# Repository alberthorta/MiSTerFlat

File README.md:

# MiSTerFlat

Everything for my flat MiSTer FPGA: the boards, the display, the web manager and the helper
scripts, in one repository.

| Folder | What it is |
|---|---|
| [`hardware/`](hardware) | The flat backplane (Rev A5) and the front panel board. KiCad projects generated by Python scripts, Gerbers, mechanical drawings. |
| [`display/`](display) | MiSTerLily: the colour status display (ESP32-S3 firmware, MiSTer daemon, installer). Website: https://alberthorta.github.io/MiSTerFlat/ |
| [`manager/`](manager) | MiSTerManager: the web page that runs on the MiSTer (games, saves, settings, display, power). |
| [`art/`](art) | Personal scripts that make the colour core pictures for the display. The pictures are not in git. |
| [`roms/`](roms) | Scripts that build MiSTer arcade ROM zips from my own ROM collection. |

Each folder has its own README with the details.

## Releases

Tags `v*` are MiSTerLily releases (firmware for every board plus `misterlily_install.sh`). The
updaters on the MiSTer read the latest release, so other parts of the repository do not use
`v*` tags. See [`.github/workflows/release.yml`](.github/workflows/release.yml).

`mister` in the root is a link to `display/mister`. MiSTerLily updaters older than this
repository look for `mister/` in the root; keep the link so they can update.

## Licence

MiSTerLily is GPL-3.0 ([`display/LICENSE`](display/LICENSE)).

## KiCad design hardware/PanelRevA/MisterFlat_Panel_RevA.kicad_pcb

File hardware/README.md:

# MisterFlat

A flat backplane that puts a QMTECH Cyclone V SoC board and its I/O Board
V2.1 side by side, instead of stacked. Used for MiSTer FPGA in a flat case.

**Status: Rev A5, prototype.** A 1:1 print was checked against the real
QMTECH boards (pins, holes, notches, JP6 pinout). See
[docs/RevA5_design_notes.md](docs/RevA5_design_notes.md).

- I/O Board on the left, upright, on two 2x20 male headers.
- Cyclone on the right, flipped (FPGA faces the backplane), on two 2x20
  female sockets. There is a window under the FPGA for the heatsink.
- J12 and J10 (GPIO_1) are passed through pin for pin.
- The Cyclone JP6 USB feeds an Adafruit 5997 (CH334F) hub. Its outputs
  go to the I/O Board, a display header, an AUX header and a USB-A for
  the Wi-Fi/BT dongle.
- A network extension on the left brings the Cyclone RJ45 (front) to the
  rear, through a short patch cable and two RJ45 jacks.
- A small front panel board (`PanelRevA/`) holds 3 buttons and 3 LEDs.
  A 12-wire IDC ribbon connects it to J24 on the backplane.

## Layout

| Path | Content |
|---|---|
| `RevA5/` | KiCad 10 project (schematic, PCB, project library) |
| `RevA5/reports/` | ERC, DRC, schematic PDF, PCB layer PDFs, BOM |
| `PanelRevA/` | Front panel board, KiCad project, reports, fab and STEP |
| `tools/design.py` | All geometry, parts and nets. Edit this file. |
| `tools/build_sch.py` | Writes the schematic and the symbol library |
| `tools/build_pcb.py` | Writes the PCB, the hub footprint and all routing |
| `tools/build_panel.py` | Writes the front panel board (schematic and PCB) |
| `tools/verify.py` | Pin-for-pin, position and length checks |
| `tools/make_outputs.sh` | Runs everything and writes all outputs of both boards |
| `docs/` | Audit of Rev A4, design notes, changelog, images |
| `handoff/` | The original package (QMTECH sources, Rev A4). Local only, not in git |
| `refs/` | Adafruit CH334F Eagle files |

## Regenerate

The KiCad files are generated. Change `tools/design.py` (or the build
scripts), then run from this `hardware/` folder:

```sh
tools/make_outputs.sh
```

It builds both boards, runs `verify.py`, ERC and DRC, and writes:

- `RevA5/fab/` and `PanelRevA/fab/`: Gerber zips for JLCPCB (see
  `RevA5/fab/README_fab.md`).
- `*/reports/`: ERC, DRC, schematic PDF, BOM and a 1:1 A4 print.
- `RevA5/mech/`: mechanical PDF (A3, 1:1, page 5 is the front panel) and
  STEP. `PanelRevA/mech/`: STEP of the front panel board.

If you edit the board by hand in KiCad, the next build overwrites it.
After the design is frozen, hand edits are fine; from then on, stop
using the scripts.

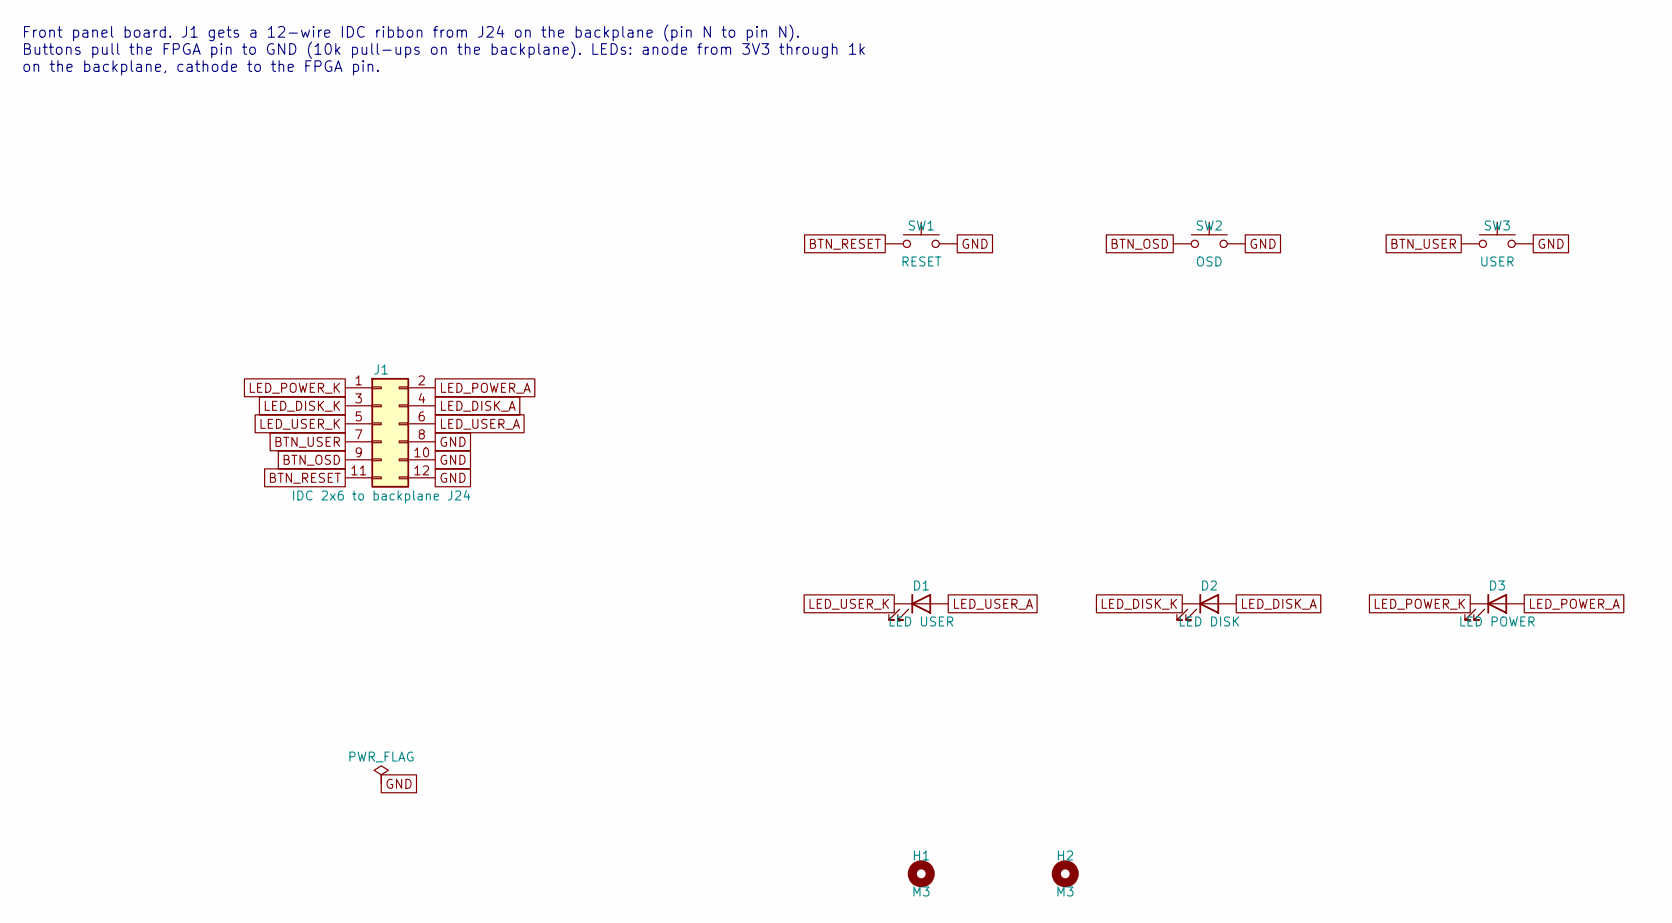
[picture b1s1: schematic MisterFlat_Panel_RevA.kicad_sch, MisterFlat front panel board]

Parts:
D1: LED USER; LED_D3.0mm; MPN 3 mm LED, 2 mA is enough (1k on the bac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
D2: LED DISK; LED_D3.0mm; MPN 3 mm LED, 2 mA is enough (1k on the bac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
D3: LED POWER; LED_D3.0mm; MPN 3 mm LED, 2 mA is enough (1k on the bac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
H1, H2: M3; MountingHole_3.2mm_M3
J1: IDC 2x6 to backplane J24; IDC-Header_2x06_P2.54mm_Vertical
SW1: RESET; SW_PUSH_6mm_H13mm; MPN 6x6 mm tactile switch, 13 mm high
SW2: OSD; SW_PUSH_6mm_H13mm; MPN 6x6 mm tactile switch, 13 mm high
SW3: USER; SW_PUSH_6mm_H13mm; MPN 6x6 mm tactile switch, 13 mm high

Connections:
BTN_OSD: J1.9, SW2.1
BTN_RESET: J1.11, SW1.1
BTN_USER: J1.7, SW3.1
GND: J1.8, J1.10, J1.12, SW1.2, SW2.2, SW3.2
LED_DISK_A: D2.2 (A), J1.4
LED_DISK_K: D2.1 (K), J1.3
LED_POWER_A: D3.2 (A), J1.2
LED_POWER_K: D3.1 (K), J1.1
LED_USER_A: D1.2 (A), J1.6
LED_USER_K: D1.1 (K), J1.5

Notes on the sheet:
Front panel board. J1 gets a 12-wire IDC ribbon from J24 on the backplane (pin N to pin N). Buttons pull the FPGA pin to GND (10k pull-ups on the backplane). LEDs: anode from 3V3 through 1k on the backplane, cathode to the FPGA pin.

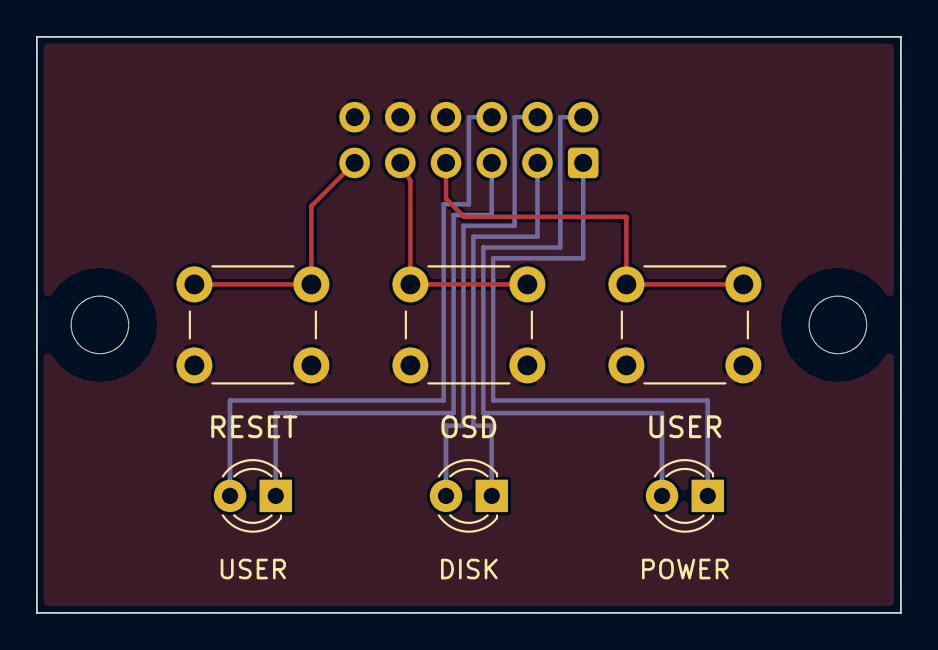
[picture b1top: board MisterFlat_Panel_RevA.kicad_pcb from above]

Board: 2 copper layers, 48.0 x 32.0 mm, 9 parts (1 on the bottom side), 10 nets.

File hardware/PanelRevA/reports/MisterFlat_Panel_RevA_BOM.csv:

"Refs","Value","Footprint","Qty","DNP"
"D1","LED USER","LED_THT:LED_D3.0mm","1",""
"D2","LED DISK","LED_THT:LED_D3.0mm","1",""
"D3","LED POWER","LED_THT:LED_D3.0mm","1",""
"J1","IDC 2x6 to backplane J24","Connector_IDC:IDC-Header_2x06_P2.54mm_Vertical","1",""
"SW1","RESET","Button_Switch_THT:SW_PUSH_6mm_H13mm","1",""
"SW2","OSD","Button_Switch_THT:SW_PUSH_6mm_H13mm","1",""
"SW3","USER","Button_Switch_THT:SW_PUSH_6mm_H13mm","1",""

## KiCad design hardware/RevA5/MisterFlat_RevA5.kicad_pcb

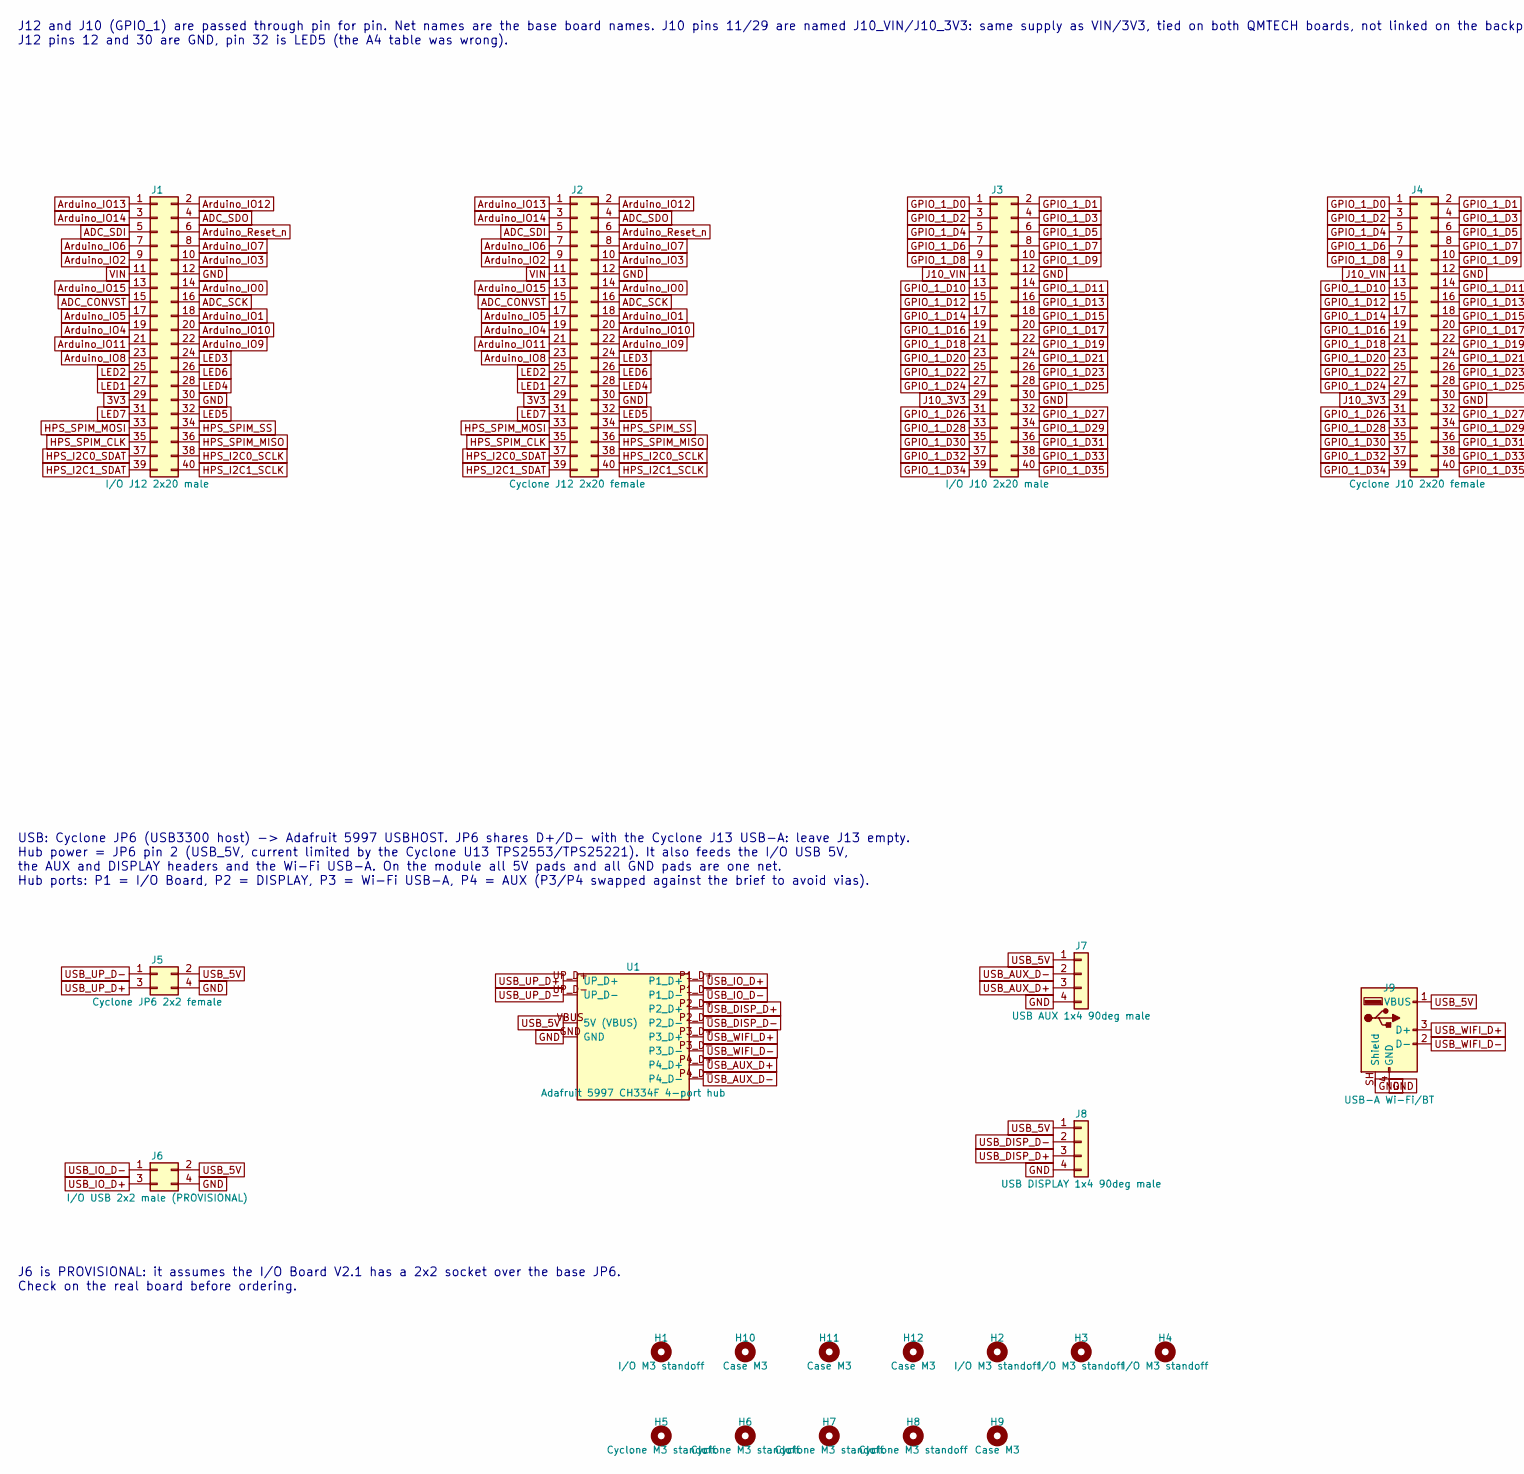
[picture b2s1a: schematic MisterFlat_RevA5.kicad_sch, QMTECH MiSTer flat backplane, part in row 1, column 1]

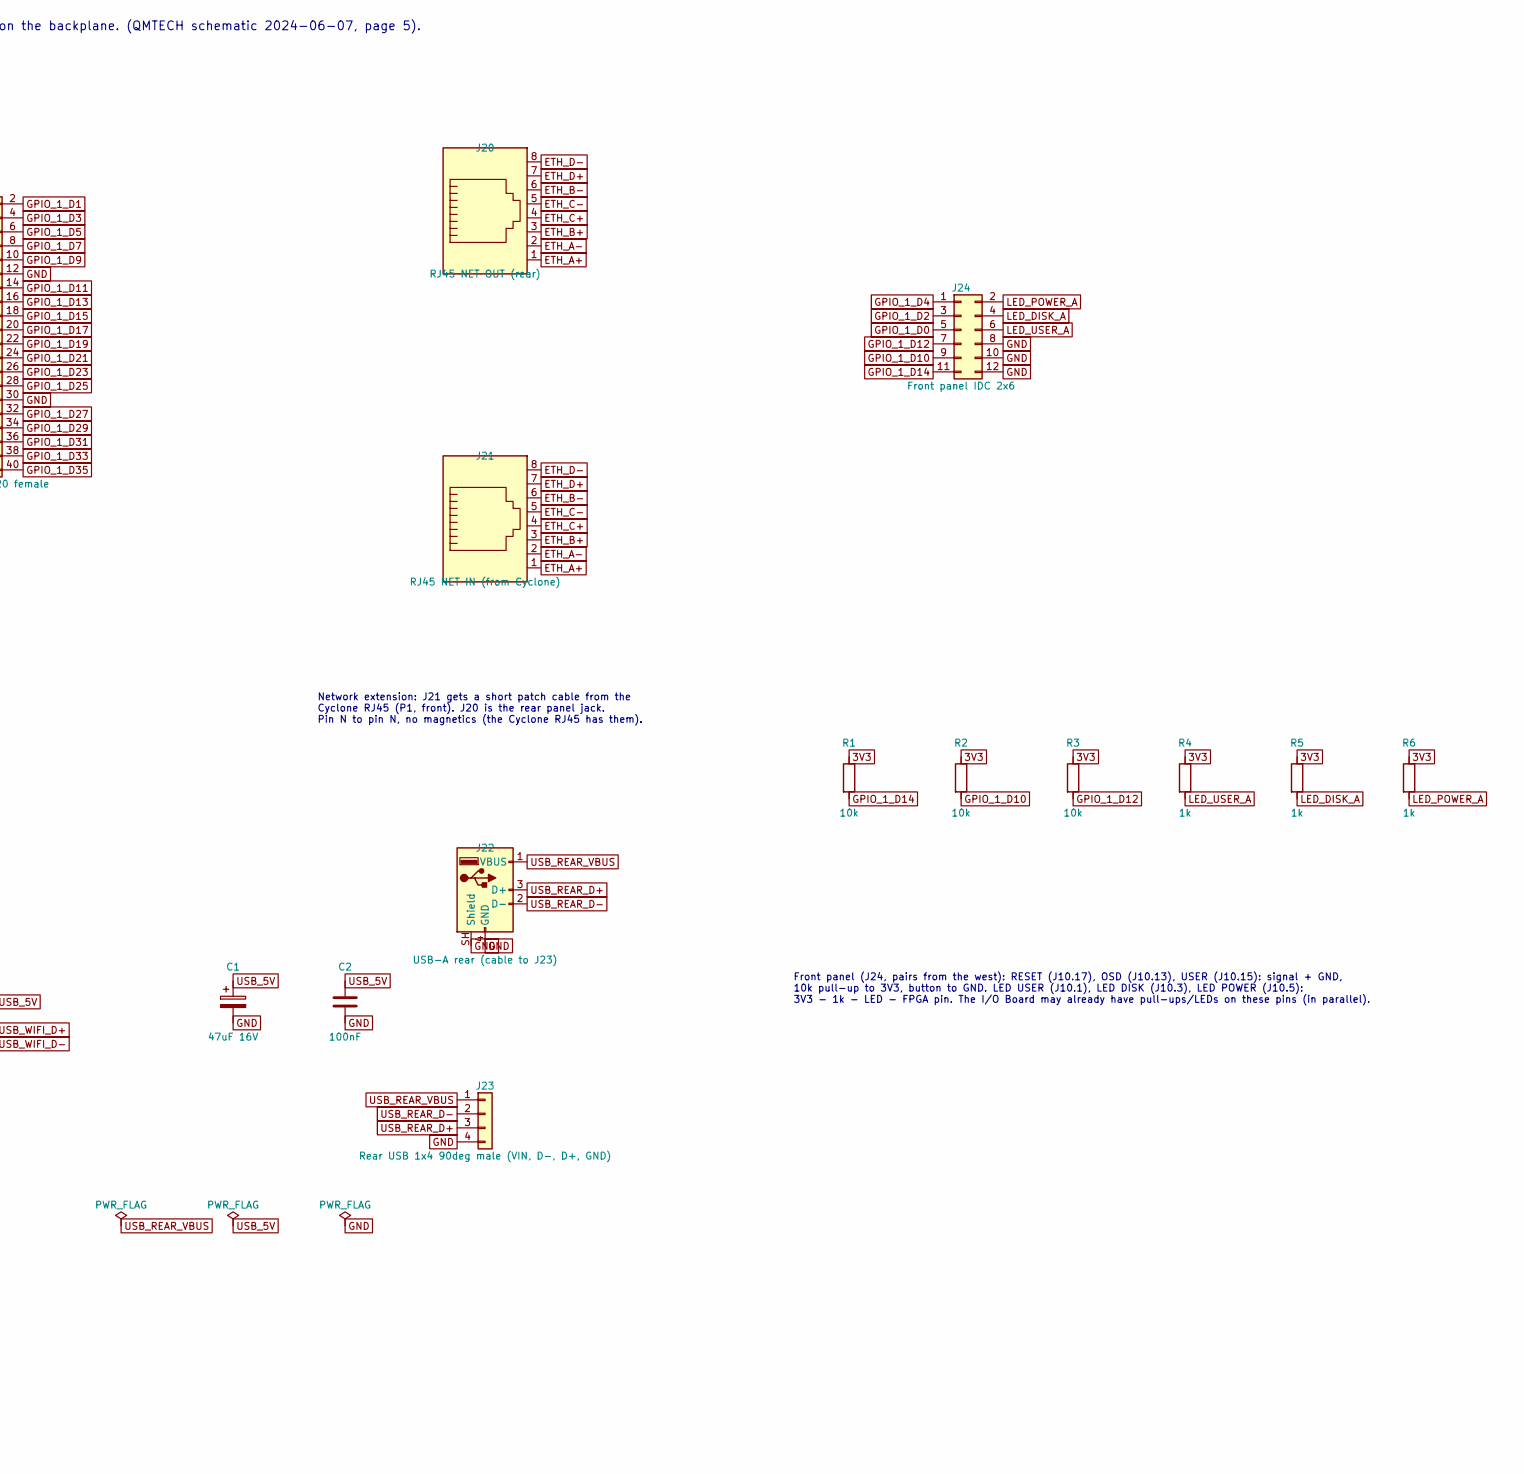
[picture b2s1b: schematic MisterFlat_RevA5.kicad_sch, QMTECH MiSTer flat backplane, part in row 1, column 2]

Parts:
C1: 47uF 16V; CP_Radial_D5.0mm_P2.00mm
C2: 100nF; C_Disc_D3.0mm_W1.6mm_P2.50mm
H1, H2, H3, H4: I/O M3 standoff; MountingHole_3.2mm_M3
H5, H6, H7, H8: Cyclone M3 standoff; MountingHole_3.2mm_M3
H9, H10, H11, H12: Case M3; MountingHole_3.2mm_M3
J1: I/O J12 2x20 male; PinHeader_2x20_P2.54mm_Vertical
J2: Cyclone J12 2x20 female; PinSocket_2x20_P2.54mm_Vertical
J3: I/O J10 2x20 male; PinHeader_2x20_P2.54mm_Vertical
J4: Cyclone J10 2x20 female; PinSocket_2x20_P2.54mm_Vertical
J5: Cyclone JP6 2x2 female; PinSocket_2x02_P2.54mm_Vertical
J6: I/O USB 2x2 male (PROVISIONAL); PinHeader_2x02_P2.54mm_Vertical
J7: USB AUX 1x4 90deg male; PinHeader_1x04_P2.54mm_Horizontal
J8: USB DISPLAY 1x4 90deg male; PinHeader_1x04_P2.54mm_Horizontal
J9: USB-A Wi-Fi/BT; USB_A_Molex_67643_Horizontal; MPN Molex 67643-0910
J20: RJ45 NET OUT (rear); RJ45_Amphenol_54602-x08_Horizontal; MPN Amphenol 54602-908 (no magnetics)
J21: RJ45 NET IN (from Cyclone); RJ45_Amphenol_54602-x08_Horizontal; MPN Amphenol 54602-908 (no magnetics)
J22: USB-A rear (cable to J23); USB_A_Molex_67643_Horizontal; MPN Molex 67643-0910
J23: Rear USB 1x4 90deg male (VIN, D-, D+, GND); PinHeader_1x04_P2.54mm_Horizontal
J24: Front panel IDC 2x6; IDC-Header_2x06_P2.54mm_Vertical
R1, R2, R3: 10k; R_Axial_DIN0207_L6.3mm_D2.5mm_P2.54mm_Vertical
R4, R5, R6: 1k; R_Axial_DIN0207_L6.3mm_D2.5mm_P2.54mm_Vertical
U1: Adafruit 5997 CH334F 4-port hub; Adafruit_5997_CH334F_Socketed

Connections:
3V3: J1.29, J2.29, R1.1, R2.1, R3.1, R4.1, R5.1, R6.1
ADC_CONVST: J1.15, J2.15
ADC_SCK: J1.16, J2.16
ADC_SDI: J1.5, J2.5
ADC_SDO: J1.4, J2.4
Arduino_IO0: J1.14, J2.14
Arduino_IO1: J1.18, J2.18
Arduino_IO2: J1.9, J2.9
Arduino_IO3: J1.10, J2.10
Arduino_IO4: J1.19, J2.19
Arduino_IO5: J1.17, J2.17
Arduino_IO6: J1.7, J2.7
Arduino_IO7: J1.8, J2.8
Arduino_IO8: J1.23, J2.23
Arduino_IO9: J1.22, J2.22
Arduino_IO10: J1.20, J2.20
Arduino_IO11: J1.21, J2.21
Arduino_IO12: J1.2, J2.2
Arduino_IO13: J1.1, J2.1
Arduino_IO14: J1.3, J2.3
Arduino_IO15: J1.13, J2.13
Arduino_Reset_n: J1.6, J2.6
ETH_A+: J20.1, J21.1
ETH_A-: J20.2, J21.2
ETH_B+: J20.3, J21.3
ETH_B-: J20.6, J21.6
ETH_C+: J20.4, J21.4
ETH_C-: J20.5, J21.5
ETH_D+: J20.7, J21.7
ETH_D-: J20.8, J21.8
GND: C1.2, C2.2, J1.12, J1.30, J2.12, J2.30, J3.12, J3.30, J4.12, J4.30, J5.4, J6.4, J7.4, J8.4, J9.4 (GND), J9.SH (Shield), J22.4 (GND), J22.SH (Shield), J23.4, J24.8, J24.10, J24.12, U1.GND
GPIO_1_D0: J3.1, J4.1, J24.5
GPIO_1_D1: J3.2, J4.2
GPIO_1_D2: J3.3, J4.3, J24.3
GPIO_1_D3: J3.4, J4.4
GPIO_1_D4: J3.5, J4.5, J24.1
GPIO_1_D5: J3.6, J4.6
GPIO_1_D6: J3.7, J4.7
GPIO_1_D7: J3.8, J4.8
GPIO_1_D8: J3.9, J4.9
GPIO_1_D9: J3.10, J4.10
GPIO_1_D10: J3.13, J4.13, J24.9, R2.2
GPIO_1_D11: J3.14, J4.14
GPIO_1_D12: J3.15, J4.15, J24.7, R3.2
GPIO_1_D13: J3.16, J4.16
GPIO_1_D14: J3.17, J4.17, J24.11, R1.2
GPIO_1_D15: J3.18, J4.18
GPIO_1_D16: J3.19, J4.19
GPIO_1_D17: J3.20, J4.20
GPIO_1_D18: J3.21, J4.21
GPIO_1_D19: J3.22, J4.22
GPIO_1_D20: J3.23, J4.23
GPIO_1_D21: J3.24, J4.24
GPIO_1_D22: J3.25, J4.25
GPIO_1_D23: J3.26, J4.26
GPIO_1_D24: J3.27, J4.27
GPIO_1_D25: J3.28, J4.28
GPIO_1_D26: J3.31, J4.31
GPIO_1_D27: J3.32, J4.32
GPIO_1_D28: J3.33, J4.33
GPIO_1_D29: J3.34, J4.34
GPIO_1_D30: J3.35, J4.35
GPIO_1_D31: J3.36, J4.36
GPIO_1_D32: J3.37, J4.37
GPIO_1_D33: J3.38, J4.38
GPIO_1_D34: J3.39, J4.39
GPIO_1_D35: J3.40, J4.40
HPS_I2C0_SCLK: J1.38, J2.38
HPS_I2C0_SDAT: J1.37, J2.37
HPS_I2C1_SCLK: J1.40, J2.40
HPS_I2C1_SDAT: J1.39, J2.39
HPS_SPIM_CLK: J1.35, J2.35
HPS_SPIM_MISO: J1.36, J2.36
HPS_SPIM_MOSI: J1.33, J2.33
HPS_SPIM_SS: J1.34, J2.34
J10_3V3: J3.29, J4.29
J10_VIN: J3.11, J4.11
LED1: J1.27, J2.27
LED2: J1.25, J2.25
LED3: J1.24, J2.24
LED4: J1.28, J2.28
LED5: J1.32, J2.32
LED6: J1.26, J2.26
LED7: J1.31, J2.31
LED_DISK_A: J24.4, R5.2
LED_POWER_A: J24.2, R6.2
LED_USER_A: J24.6, R4.2
USB_5V: C1.1, C2.1, J5.2, J6.2, J7.1, J8.1, J9.1 (VBUS), U1.VBUS (5V (VBUS))
USB_AUX_D+: J7.3, U1.P4_D+
USB_AUX_D-: J7.2, U1.P4_D-
USB_DISP_D+: J8.3, U1.P2_D+
USB_DISP_D-: J8.2, U1.P2_D-
USB_IO_D+: J6.3, U1.P1_D+
USB_IO_D-: J6.1, U1.P1_D-
USB_REAR_D+: J22.3 (D+), J23.3
USB_REAR_D-: J22.2 (D-), J23.2
USB_REAR_VBUS: J22.1 (VBUS), J23.1
USB_UP_D+: J5.3, U1.UP_D+
USB_UP_D-: J5.1, U1.UP_D-
USB_WIFI_D+: J9.3 (D+), U1.P3_D+
USB_WIFI_D-: J9.2 (D-), U1.P3_D-
VIN: J1.11, J2.11

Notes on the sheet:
Network extension: J21 gets a short patch cable from the Cyclone RJ45 (P1, front). J20 is the rear panel jack. Pin N to pin N, no magnetics (the Cyclone RJ45 has them).
Front panel (J24, pairs from the west): RESET (J10.17), OSD (J10.13), USER (J10.15): signal + GND, 10k pull-up to 3V3, button to GND. LED USER (J10.1), LED DISK (J10.3), LED POWER (J10.5): 3V3 - 1k - LED - FPGA pin. The I/O Board may already have pull-ups/LEDs on these pins (in parallel).
J12 and J10 (GPIO_1) are passed through pin for pin. Net names are the base board names. J10 pins 11/29 are named J10_VIN/J10_3V3: same supply as VIN/3V3, tied on both QMTECH boards, not linked on the backplane. (QMTECH schematic 2024-06-07, page 5). J12 pins 12 and 30 are GND, pin 32 is LED5 (the 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
USB: Cyclone JP6 (USB3300 host) -> Adafruit 5997 USBHOST. JP6 shares D+/D- with the Cyclone J13 USB-A: leave J13 empty. Hub power = JP6 pin 2 (USB_5V, current limited by the Cyclone U13 TPS2553/TPS25221). It also feeds the I/O USB 5V, the AUX and DISPLAY headers and the Wi-Fi USB-A. On the module a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
J6 is PROVISIONAL: it assumes the I/O Board V2.1 has a 2x2 socket over the base JP6. Check on the real board before ordering.

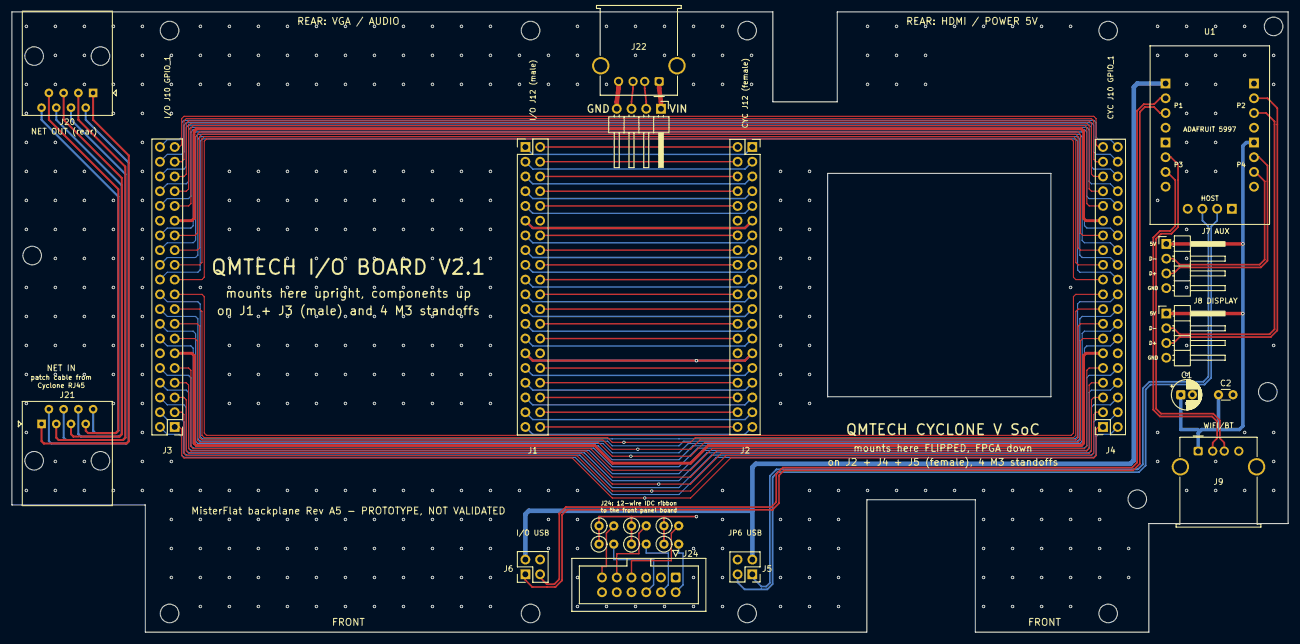
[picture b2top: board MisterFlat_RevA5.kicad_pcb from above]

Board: 4 copper layers, 220.0 x 106.9 mm, 35 parts (0 on the bottom side), 102 nets.
